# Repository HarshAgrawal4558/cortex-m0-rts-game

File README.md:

# Cortex-M0+ RTS Game

A custom real-time strategy video game running on a Cortex-M0+ microcontroller. It has custom-designed hardware and UART-based wireless multiplayer.

## Overview

This project was built for an embedded systems lab course (Jan 2024 - May 2024). It covers the full stack: C++ firmware, a custom PCB, and a wireless link that lets multiple players interact in real time.

## Features

- Real-time strategy gameplay on a resource-constrained microcontroller
- Wireless multi-user interaction over UART
- Custom PCB with optimized component selection and I/O design
- Firmware tuned for low latency and efficient CPU use

## System Architecture

```
Player input ──► Game logic ──► Display / Audio output
                     │
                     ▼
              UART wireless link ◄──► Other player's unit
```

## Hardware

- **Microcontroller:** Cortex-M0+
- **Communication:** UART with a wireless module
- **Input:** `<buttons / joystick>`
- **Output:** `<display / speaker>`

Schematics and layout files are in [`hardware/`](hardware/).

## Repository Structure

```
cortex-m0-rts-game/
├── firmware/      # C++ source code
├── hardware/      # Altium schematics, PCB layout, BOM
├── docs/          # Photos, demo media, design notes
└── README.md
```

## Getting Started

### Prerequisites

- `<Toolchain, e.g. Code Composer Studio>`
- `<Programmer / debugger>`

### Multiplayer Setup

1. Flash the firmware onto two or more boards.
2. Power each board and confirm the UART wireless link is active.
3. Start a game from any unit. The others join automatically.

## Design Notes

- **Efficiency:** _e.g. fixed-point math, interrupt-driven input, minimal redraws_
- **UART latency:** _e.g. packet format, baud rate, buffering strategy_
- **Hardware:** _e.g. component choices, routing decisions for signal integrity_

## Future Work

- Additional units and game mechanics
- Improved graphics and sound
- Support for more than two players

## Author

**Harsh Agrawal**, B.S. Electrical and Computer Engineering, The University of Texas at Austin
[LinkedIn](https://linkedin.com/in/ha-agrawal)

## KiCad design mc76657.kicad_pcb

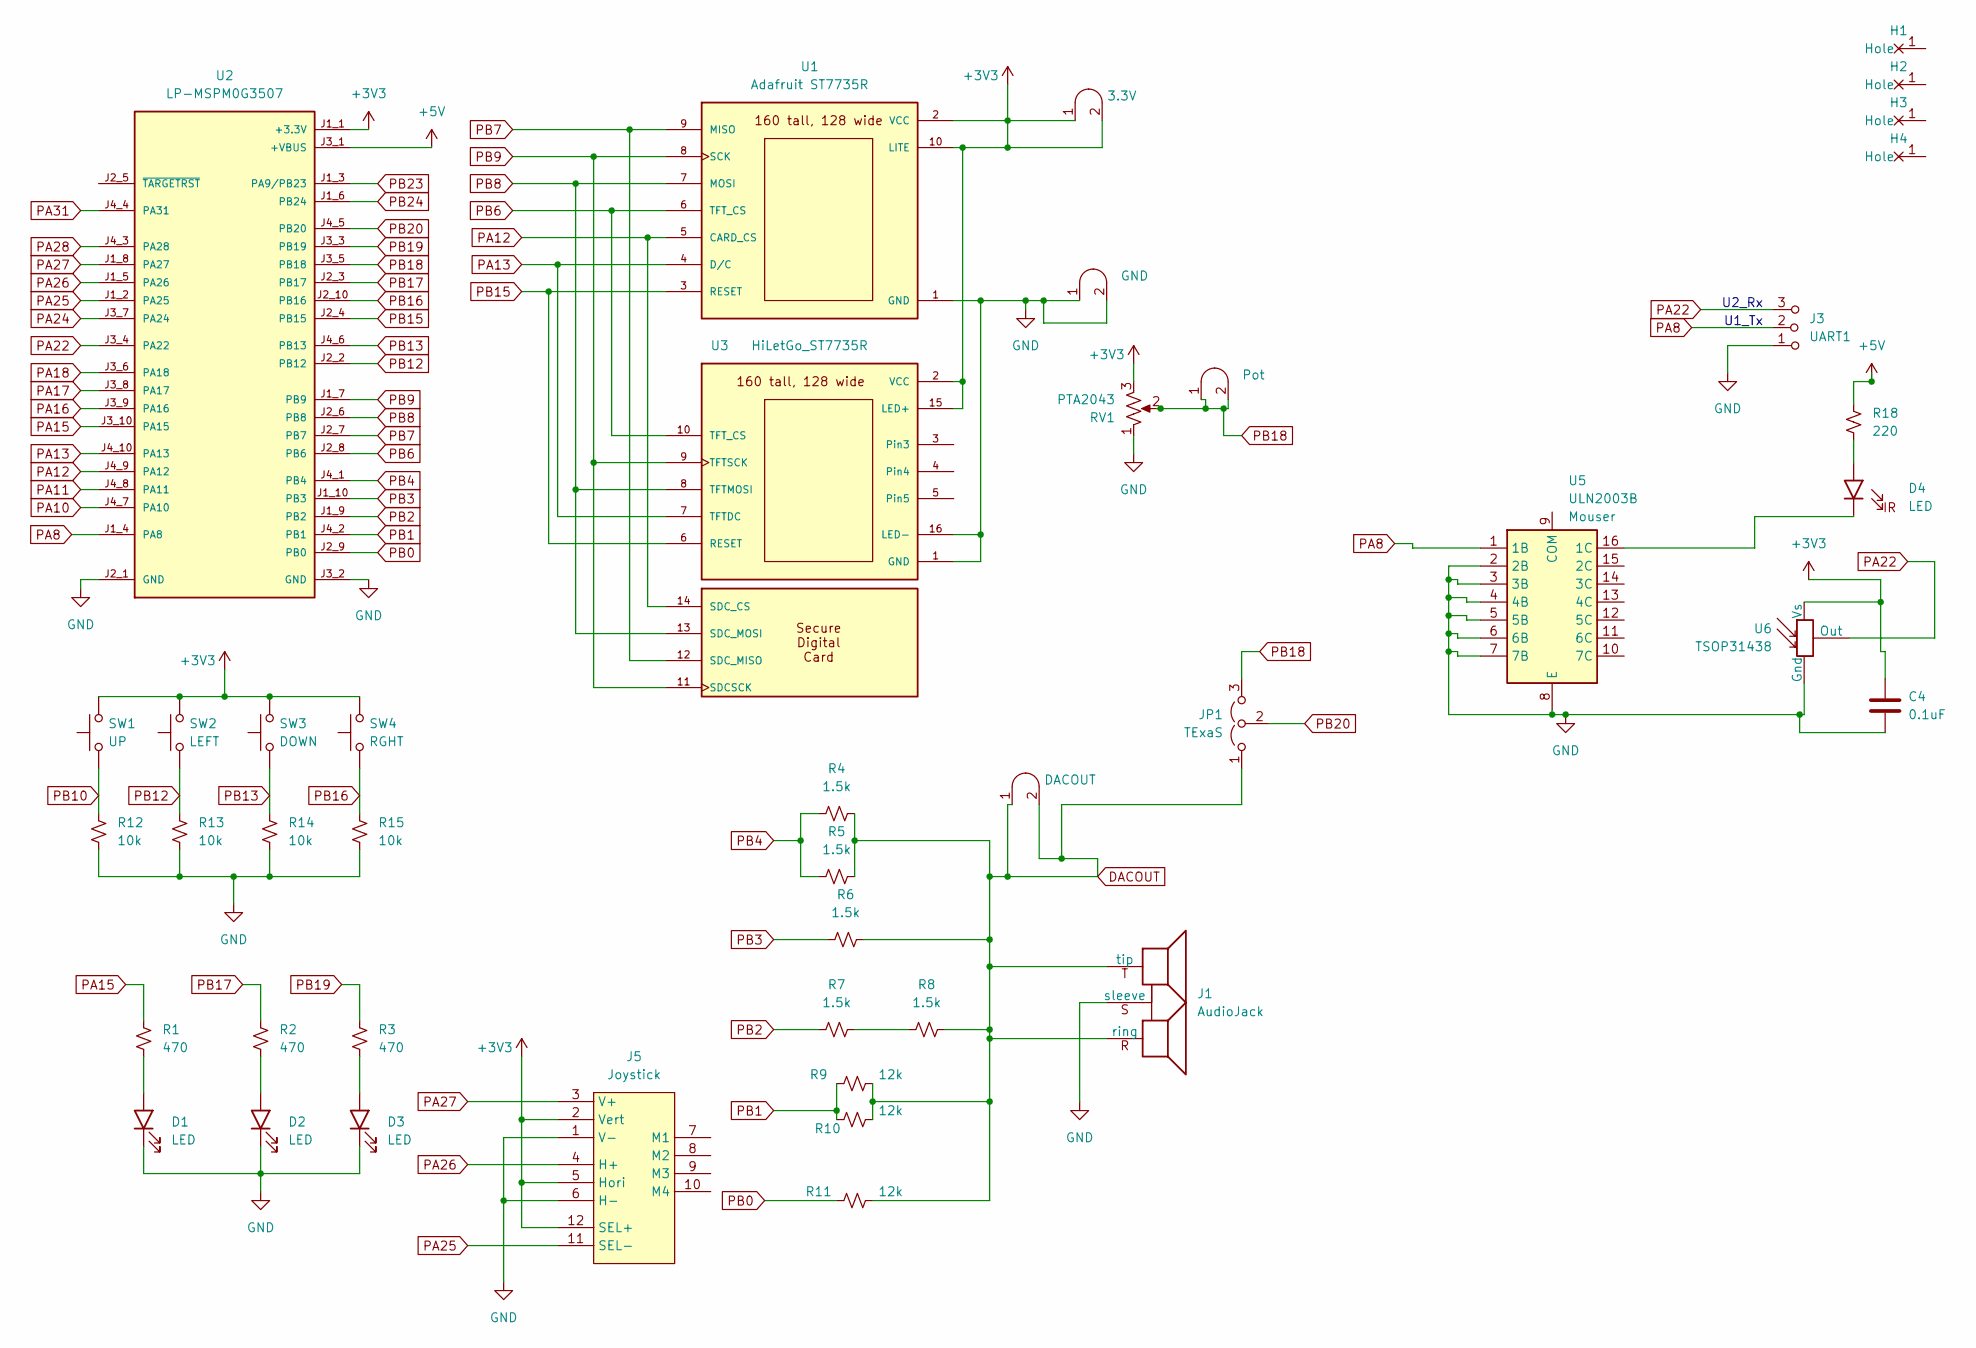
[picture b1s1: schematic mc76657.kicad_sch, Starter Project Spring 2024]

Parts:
C4: 0.1uF; C_Axial_200mil
D1, D2, D3, D4: LED; LED_D5.0mm
H1, H2, H3, H4: MountingHole_4_40
J1: AudioJack; Jack_3.5mm_CUI_SJ1-3523N_Horizontal
J2: DACOUT; Testpoint_1x02_P2.54mm
J3: UART1; PinHeader_1x03_P2.54mm_Vertical
J4: Pot; Testpoint_1x02_P2.54mm
J5: Joystick; SparkfunJoystick
J6: GND; Testpoint_1x02_P2.54mm
JP1: TExaS; PinHeader_1x03_P2.54mm_Vertical
R1, R2, R3: 470; R_Axial_DIN0204_L3.6mm_D1.6mm_P7.62mm_Horizontal
R4, R5, R6, R7, R8: 1.5k; R_Axial_DIN0204_L3.6mm_D1.6mm_P7.62mm_Horizontal
R9, R10, R11: 12k; R_Axial_DIN0204_L3.6mm_D1.6mm_P7.62mm_Horizontal
R12, R13, R14, R15: 10k; R_Axial_DIN0204_L3.6mm_D1.6mm_P7.62mm_Horizontal
R18: 220; R_Axial_DIN0204_L3.6mm_D1.6mm_P7.62mm_Horizontal
RV1: PTA2043; PTA2043pot
SW1: UP; SW_PUSH_6mm
SW2: LEFT; SW_PUSH_6mm
SW3: DOWN; SW_PUSH_6mm
SW4: RGHT; SW_PUSH_6mm
TP1: 3.3V; Testpoint_1x02_P2.54mm
U1: Adafruit ST7735R; adafruit_st7735r
U2: LP-MSPM0G3507; ti_LP_MSPM0G3507
U3: HiLetGo_ST7735R; hiletgo_st7735r
U5: ULN2003B; DIP-16_W7.62mm
U6: TSOP31438

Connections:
+3V3: C4.1, J5.2 (Vert), J5.5 (Hori), J5.12 (SEL+), RV1.3, SW1.2, SW2.2, SW3.2, SW4.2, TP1.1 (A), TP1.2 (B), U1.2 (VCC), U1.10 (LITE), U2.J1_1 (+3.3V), U3.2 (VCC), U3.15 (LED+), U6.2 (Vs); also elsewhere on the board
+5V: R18.1, U2.J3_1 (+VBUS)
DACOUT: J1.R (ring), J1.T (tip), J2.1 (A), J2.2 (B), JP1.1 (A), R4.1, R5.1, R6.1, R8.1, R9.1, R10.1, R11.1
GND: C4.2, D1.1 (K), D2.1 (K), D3.1 (K), J1.S (sleeve), J3.1 (A), J5.1 (V-), J5.6 (H-), J6.1 (A), J6.2 (B), R12.2, R13.2, R14.2, R15.2, RV1.1, U1.1 (GND), U2.J2_1 (GND), U2.J3_2 (GND), U3.1 (GND), U3.16 (LED-), U5.2 (2B), U5.3 (3B), U5.4 (4B), U5.5 (5B), U5.6 (6B), U5.7 (7B), U5.8 (E), U6.1 (Gnd); also elsewhere on the board
unnamed: D1.2 (A), R1.2
unnamed: D2.2 (A), R2.2
unnamed: D3.2 (A), R3.2
unnamed: D4.2 (A), R18.2
unnamed: D4.1 (K), U5.16 (1C)
unnamed: R7.1, R8.2
PA8: J3.2 (B), U2.J1_4 (PA8), U5.1 (1B)
PA10: U2.J4_7 (PA10)
PA11: U2.J4_8 (PA11)
PA12: U1.5 (CARD_CS), U2.J4_9 (PA12), U3.14 (SDC_CS); also elsewhere on the board
PA13: U1.4 (D/C), U2.J4_10 (PA13), U3.7 (TFTDC); also elsewhere on the board
PA15: R1.1, U2.J3_10 (PA15)
PA16: U2.J3_9 (PA16)
PA17: U2.J3_8 (PA17)
PA18: U2.J3_6 (PA18)
PA22: J3.3 (C), U2.J3_4 (PA22), U6.3 (Out)
PA24: U2.J3_7 (PA24)
PA25: J5.11 (SEL-), U2.J1_2 (PA25); also elsewhere on the board
PA26: J5.4 (H+), U2.J1_5 (PA26); also elsewhere on the board
PA27: J5.3 (V+), U2.J1_8 (PA27); also elsewhere on the board
PA28: U2.J4_3 (PA28)
PA31: U2.J4_4 (PA31)
PB0: R11.2, U2.J2_9 (PB0)
PB1: R9.2, R10.2, U2.J4_2 (PB1)
PB2: R7.2, U2.J1_9 (PB2)
PB3: R6.2, U2.J1_10 (PB3)
PB4: R4.2, R5.2, U2.J4_1 (PB4)
PB6: U1.6 (TFT_CS), U2.J2_8 (PB6), U3.10 (TFT_CS); also elsewhere on the board
PB7: U1.9 (MISO), U2.J2_7 (PB7), U3.12 (SDC_MISO); also elsewhere on the board
PB8: U1.7 (MOSI), U2.J2_6 (PB8), U3.8 (TFTMOSI), U3.13 (SDC_MOSI); also elsewhere on the board
PB9: U1.8 (SCK), U2.J1_7 (PB9), U3.9 (TFTSCK), U3.11 (SDCSCK); also elsewhere on the board
PB10: R12.1, SW1.1
PB12: R13.1, SW2.1, U2.J2_2 (PB12)
PB13: R14.1, SW3.1, U2.J4_6 (PB13)
PB15: U1.3 (RESET), U2.J2_4 (PB15), U3.6 (RESET); also elsewhere on the board
PB16: R15.1, SW4.1, U2.J2_10 (PB16)
PB17: R2.1, U2.J2_3 (PB17)
PB18: J4.1 (A), J4.2 (B), JP1.3 (B), RV1.2, U2.J3_5 (PB18)
PB19: R3.1, U2.J3_3 (PB19)
PB20: JP1.2 (C), U2.J4_5 (PB20)
PB23: U2.J1_3 (PA9/PB23)
PB24: U2.J1_6 (PB24)

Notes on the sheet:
U1_Tx
U2_Rx

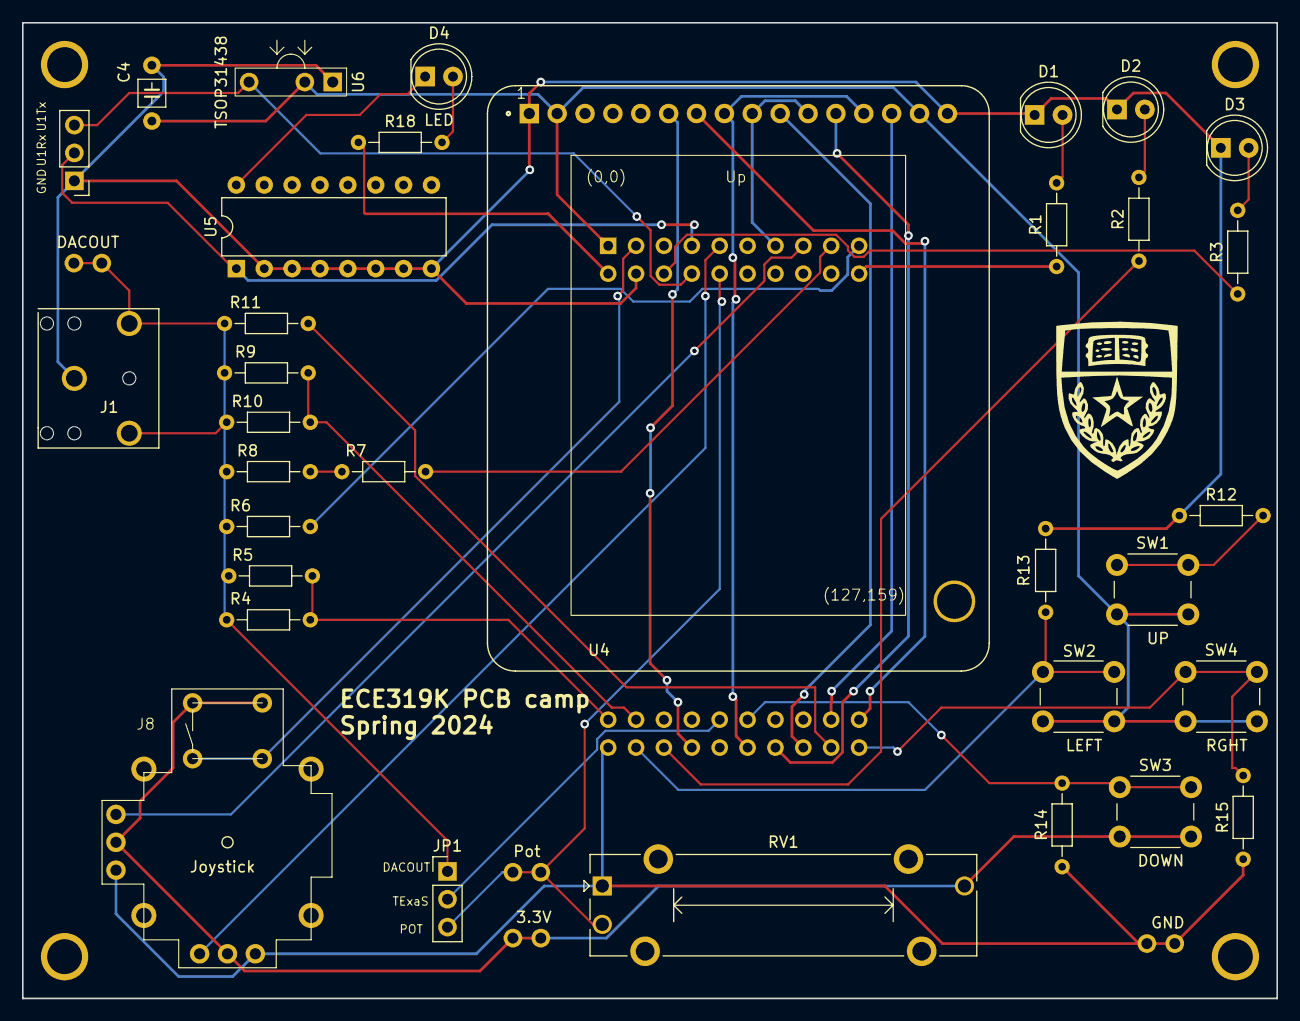
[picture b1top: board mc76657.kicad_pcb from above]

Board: 2 copper layers, 114.3 x 88.9 mm, 42 parts (1 on the bottom side), 36 nets.

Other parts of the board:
J8: Joystick; SparkfunJoystick
U4: HiLetGo_ST7735R; hiletgo_st7735r

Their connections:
+3V3: J8.2 (Vert), J8.5 (Hori), J8.12 (SEL+), U4.2 (VCC), U4.15 (LED+); also elsewhere on the board
GND: J8.1 (V-), J8.6 (H-), U4.1 (GND), U4.16 (LED-); also elsewhere on the board
PA12: U4.14 (SDC_CS); also elsewhere on the board
PA13: U4.7 (TFTDC); also elsewhere on the board
PA25: J8.11 (SEL-); also elsewhere on the board
PA26: J8.4 (H+); also elsewhere on the board
PA27: J8.3 (V+); also elsewhere on the board
PB6: U4.10 (TFT_CS); also elsewhere on the board
PB7: U4.12 (SDC_MISO); also elsewhere on the board
PB8: U4.8 (TFTMOSI), U4.13 (SDC_MOSI); also elsewhere on the board
PB9: U4.9 (TFTSCK), U4.11 (SDCSCK); also elsewhere on the board
PB15: U4.6 (RESET); also elsewhere on the board

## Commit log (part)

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2024-04-19 Update images.h
    blastoise and pikachu
2024-04-20 images.h
2024-04-20 Add files via upload
    the .h files
2024-04-20 Update images.h
    explosion
2024-04-20 test
2024-04-20 more sounds (5 bit precision)
2024-04-21 joystick ADC conversion implemented.
2024-04-22 select arrow image
2024-04-22 various changes to joystick and button hover code, small arrow image
2024-04-22 minor modification to joystick
2024-04-22 using pointers instead of references for joystick
2024-04-23 changed joystick.cpp to use slide potentiometer input.
2024-04-23 implemented Slidepot_Option which will divide the slidepot ADC values into returnable regions
2024-04-23 fixed minor error
2024-04-24 major fixes to slidepot code and a test main implemented.
2024-04-24 added dialogue array to output to screen. yet to be tested.
2024-04-24 created several animation functions for sprites
2024-04-24 added sine wave sound
